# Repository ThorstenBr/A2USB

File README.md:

# A2USB: Apple II USB Interface & Apple II Mouse Interface Card

This projects provides alternate firmware for A2VGA cards to support a USB interface instead of VGA output. It currently supports a USB mouse and fully emulates an *Apple II Mouse Interface Card*.

A normal USB mouse can be used with the Apple II. The emulated *Mouse Interface Card* works well with applications like...

* ... **MousePaint**:

* ... or **A2Desktop**:

... and other similar software.

# Hardware
## Required basics

* You need a simple **MicroUSB to USB-A adpater**, so you can connect a standard USB mouse to the PICO's USB connector.

    * Either use an adapter cable:

    * Or a simple plug adapter:

* And you need a **standard USB mouse**. Anything conforming to the common "USB HID" standard should work.
* You can also use a **wireless mouse**. Their tiny transceiver plugs also implement a standard USB HID interface.

## Supported PCBs
The following boards can be used to run the A2USB firmware. Some of them require modification:

* [A2VGA PCBs](https://github.com/rallepalaveev/analog) by Ralle Palaveev, using DIP ICs. PCB Rev 1.6 and newer already have the options required for A2USB (see jumper options).
  * His v1.5 PCBs (or older) can also be used, however, they need to be modified to support A2USB. See [modifications](HwModding.md).

* David Kuder's [A2analog PCBs](https://github.com/V2RetroComputing/analog) can also be used, but currently also require the [modifications](HwModding.md).

* More supported hardware platforms are coming! Watch this spot... :)

# Installation
* Download the latest A2USB firmware ZIP file from the [Releases](https://github.com/ThorstenBr/A2USB/releases) section.
   * ZIP file contains separate firmware for NTSC/PAL regions. Difference is only the default mouse interrupt frequency (PAL 50Hz / NTSC 60Hz).
   * According to Apple II Technical Notes, the original Mouse Interface Card was also shipped with variants for PAL / NTSC, with differing default interrupt rates.
* **Remove the PICO (or entire card) from the Apple II**.
* Connect the PICO's USB to your PC/MAC **while pressing the BOOTSEL button**.
* Drag & drop the A2USB firmware file **A2USB-MOUSE-...-4ns.uf2** from the Releases ZIP archive to your PICO.
* Wait a second.
* Disconnect and reinstall in your Apple II. Route the USB adapter cable through an opening in the back. Connect a USB mouse directly (sorry, no USB HUB support yet).
* **No change to the PAL/CPLD logic is required.**

# Behind the Scenes

## How the original Apple II Mouse Interface Card worked...
The original Apple II Mouse Interface Card was introduced in 1984, shortly after the first Mac was launched. It consisted of a "peripheral interface adapter" (PIA) using an Motorila MC6821. Cards were also made using compatible Rockwell 6520/6521 PIAs. And it came with an MC6805 microcontroller as a slave device.

The microcontroller monitored the mouse buttons and movements and communicated with the Apple II's 6502 through one of the PIA's 8bit ports. It's using a very simple command based protocol: the 6502 sends commands, the slave controller responds with the requested data.

The card also had a 2KB ROM, which was mapped to the slot's 256byte address window. The ROM is split into 8 pages, which are also selected through I/O ports of the PIA. The ROM contains the necessary driver routines to communicate with the 6805 slave controller.

The card also had an option to trigger an interrupt, to notify the 6502. This interrupt could also be configured to be periodic - and synchronous to the vertical screen blanking. This ensured the mouse cursor was only updated during the screen blanking, which avoided flickering when moving the mouse.

### Here's the original Apple II Mouse Interface Card design:

                            +-----------+                                       +--------------+
                         ___|  2KB ROM  |                             __________|Apple II Mouse|
    +------+            /   +-----------+                            /          +--------------+
    | 6502 |___________/         | page selection                 |plug|
    | CPU  |\ Apple    \    +-----------+                  +------+----+-----+
    +------+ \ Bus      \___|    PIA    |__________________|     MC6805      |
              \             |  MC6821   | 8bit + handshake | MicroController |
               \            +-----------+ data             +-----------------+
             IRQ\_______________________________________________/

## How A2USB emulates the Apple II Mouse Card
The A2USB firmware uses the original code from the A2VGA project to interface the 6502 bus. It is based on the PICO's I/O slave units (PIOs), which are extremely fast I/O state machines. They control the PICO's GPIO lines and guarantee that the signals comply with the 6502 bus timing. Once the PIOs detect a 6502 READ or WRITE bus cycle, they pack the bits into a single 32bit message (containing address + data + control bits) and forward the request to the PICO's main ARM CPU.

One of the PICO's ARM cores takes care of processing incomming READ/WRITE messages. Reads are most critical, their result must be ready within about 300ns and returned to the PIOs, so the data is presented on the 6502 data bus. That's not much time. The software for the ARM cores needs to be very quick - less than 100 instruction cycles must be enough to process each message.

A few nanoseconds time have to be enough for the mouse card's ROM emulation. This is easy: the Mouse Interface Card's 2KB ROM is just an array, where we need to look up and return a single byte, whenever the 6502 makes a matching read request.
It just needs to consider the slot ROM address given by the 6502 (8bit offset) and the selected ROM page (depending on the configuration of the virtual PIA).

The same core also takes care of emulating the PIA. This is also easy. The PIA just has a couple of simple data and control registers, which can be read & written.

The PICO's second ARM core runs the "tinyUSB host" library, which interfaces with *USB HID devices* like mice (or keyboards).

The second core also emulates the mouse card's MC6805 microcontroller. This is not done on CPU instruction level, since running the original code wouldn't make much sense. Instead, the software just emulates the original communication protocol. It implements the same commands and provides the same type of responses, as the original MC6805 controller did.
And it talks to the first ARM core through the emulated PIA registers, using shared memory communication.

### This is how the design of the A2USB firmware looks:

                      +----------------------------------------------------------------------------+
                      |                         PICO Micro Controller (RP2040)                     |
     +------+         |     +----------+           +-----------------+        +------------------+ |
     | 6502 |_________|_____| PIO 1+2  |___________|   ARM Core #1   |________|   ARM Core #2    | |
     | CPU  |\ Apple  |GPIO |I/O State |   32bit   | Mouse Card ROM+ | Shared |  USB HID Stack+  | |
     +------+ \ Bus   |Pins | Machines |  Message  |  PIA Emulation  | Memory | MC6805 Emulation | |
               \      |     +----------+   FIFOs   +-----------------+        +--------+---------+ |
             IRQ\_____|_________________________________________________________/   USB|PORT       |
                      +----------------------------------------------------------------|-----------+
                                                                                       |
                                                                                       |  +-----------+
                                                                                        \-| USB MOUSE |
                                                                                          +-----------+ 

# Acknowledgements
This is an alternate firmware project for A2VGA cards to support a USB interface and Apple II Mouse Card emulation, instead of VGA output.

It is based on the A2VGA projects of...

* ... Mark Aikens: [Apple II VGA project](https://github.com/markadev/AppleII-VGA/)
* ... David Kuder: [A2analog project](https://github.com/V2RetroComputing/analog)
* ... and Ralle Palaveev: [A2VGA project](https://github.com/rallepalaveev/analog)

Many thanks for the excellent work, which is a base for the A2USB project!

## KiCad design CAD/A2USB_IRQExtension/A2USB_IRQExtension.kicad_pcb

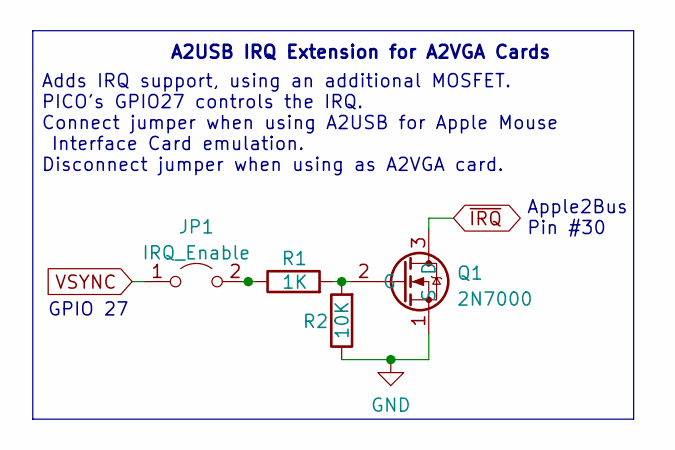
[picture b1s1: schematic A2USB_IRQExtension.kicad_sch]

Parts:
JP1: IRQ_Enable; PinHeader_1x02_P2.54mm_Vertical
Q1: 2N7000; TO-92_Inline
R1: 1K; R_Axial_DIN0207_L6.3mm_D2.5mm_P7.62mm_Horizontal
R2: 10K; R_Axial_DIN0207_L6.3mm_D2.5mm_P7.62mm_Horizontal

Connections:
GND: Q1.1 (S), R2.1
unnamed: JP1.2 (B), R1.1
unnamed: Q1.2 (G), R1.2, R2.2
VSYNC: JP1.1 (A)
~IRQ: Q1.3 (D)

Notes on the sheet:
Apple2Bus Pin #30
GPIO 27
Adds IRQ support, using an additional MOSFET. PICO's GPIO27 controls the IRQ. Connect jumper when using A2USB for Apple Mouse Interface Card emulation. Disconnect jumper when using as A2VGA card.
A2USB IRQ Extension for A2VGA Cards

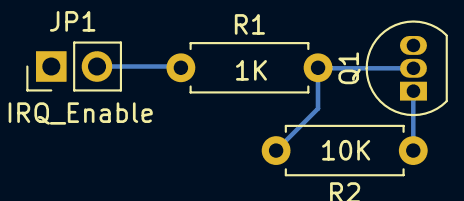
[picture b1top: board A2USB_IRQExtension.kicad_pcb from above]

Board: 2 copper layers, 4 parts (0 on the bottom side), 3 nets.

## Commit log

2024-01-01 Create git repository for upload.
2024-01-01 Added optional custom GAL. This is probably not needed. I created this originally when I was troubleshooting issues with the bus timing. It simplifies the bus interface and disables the extended slot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
2024-01-01 Added README.
2024-01-01 Added MOUSE.SAMPLE program from the Mouse Interface Card manual for testing.
2024-01-02 Added HGR variant of the simple MOUSE.DRAW example to the tests.
2024-01-02 Various minor optimizations.
2024-01-02 Makefile cleanup. Removed dependencies to tinyUSB example files.
2024-01-02 Added profiling option to test firmware. Execution time is measured based on sysclock timer. LED briefly blinks when core 1 execution time exceeds 300ns. Profiling remains disabled for the default bu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
2024-01-04 Fixed missing connection in schematic.
2024-01-04 Corrected byte-order of parameters for POSMOUSE command.
2024-01-04 Added support for "GETCLAMP" workaround From 1986, Apple II Technical Notes: as a workaround for a missing "GET_CLAMP" command, Apple documented an internal command to read memory of the slave contro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
2024-01-04 Adapt VBL behavior to manual: VBL IRQs were triggered, even when the global enable flag was OFF. The VBL flag is enough to enable this interrupt. However, the other IRQs did require the global enable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
2024-01-04 Set new version: 1.1.
2024-01-07 Project directory reogranisation. Preparations for multi-platform support...
2024-01-07 Provided separate builds for PAL/NTSC. Just differs in the default frequency for VBL interrupts. Apple II Technical Notes suggest Mouse Interface Cards were separately configured for NTSC vs PAL regi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
2024-01-07 Updated description/READMEs.
2024-01-07 Added more PCB photos...
2024-01-08 Update README.md
    Added functional description.
2024-01-08 Update README.md
    Minor README updates.
2024-01-09 Implemented VBL synchronous mouse interrupts. The periodic mouse interrupt is now synchronous to the PAL/NTSC vertical blanking as it should be. The proper timing is achieved since the board "sees" e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
2024-01-21 Added documentation only.
2024-02-04 Corrected link to "Releases".
2024-02-08 Minor clean-up.
2024-02-08 Typos + comments
2024-02-08 Added CMake option for LED mode.
2024-02-08 Trigger compile-time error when PIO code is too large.
2024-02-08 Use fast slew rate and allow higher current when controlling bus transceivers. Slightly faster PICO outputs, to speed up the bus transceivers.
